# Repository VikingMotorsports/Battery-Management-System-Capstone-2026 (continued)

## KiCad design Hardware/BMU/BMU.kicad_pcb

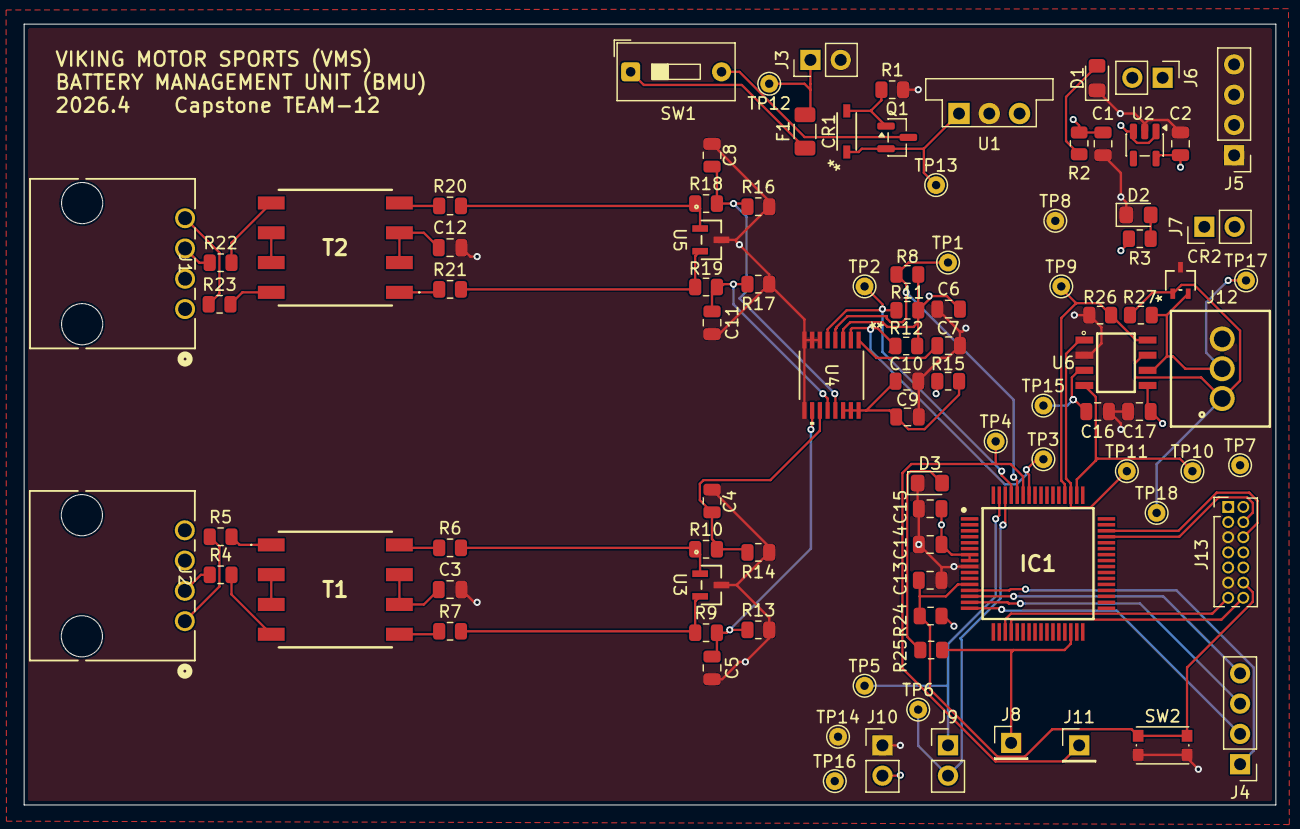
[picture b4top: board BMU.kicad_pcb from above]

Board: 4 copper layers, 105.0 x 65.5 mm, 93 parts (0 on the bottom side), 58 nets.

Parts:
C1, C2, C14: 1u; C_0805_2012Metric
C3, C4, C5, C8, C11, C12: 100pF; C_0805_2012Metric
C6, C10: 0.1u; C_0805_2012Metric
C7, C9: 0.22u; C_0805_2012Metric
C13, C15, C16, C17: 100n; C_0805_2012Metric
CR1: MMSZ5245B-7-F; SOD123_DIO
CR2: ESDCAN03-2BWY; SOT323-3L_STM
D1, D2, D3: LED; LED_0805_2012Metric_Pad1.15x1.40mm_HandSolder
F1: Fuse; Fuse_1206_3216Metric
IC1: STM32C092RCT6; QFP50P1200X1200X160-64N
J1: HIGH SIDE; CONN_70551-xxxx_04_MOL
J2: LOW SIDE; CONN_70551-xxxx_04_MOL
J3: POWER; PinHeader_1x02_P2.54mm_Vertical
J4: GPIO; PinHeader_1x04_P2.54mm_Vertical
J5: GND; PinHeader_1x04_P2.54mm_Vertical
J6: 5V; PinHeader_1x02_P2.54mm_Vertical
J7: 3V3; PinHeader_1x02_P2.54mm_Vertical
J8: FAULT; PinHeader_1x01_P2.54mm_Vertical
J9: I2C; PinHeader_1x02_P2.54mm_Vertical
J10: SHUNT; PinHeader_1x02_P2.54mm_Vertical
J11: ALERT; PinHeader_1x01_P2.54mm_Vertical
J12: CAN; 691382000003
J13: Conn_ST_STDC14; PinHeader_2x07_P1.27mm_Vertical
Q1: DMP3099L; SOT-23
R1, R8, R11: 100k; R_0805_2012Metric
R2, R3, R25: 1k; R_0805_2012Metric
R4, R5, R6, R7, R20, R21, R22, R23: 0; R_0805_2012Metric
R9, R10, R18, R19: 51; R_0805_2012Metric
R12, R24, R26: 10k; R_0805_2012Metric
R13, R14, R16, R17: 499; R_0805_2012Metric
R15: 10; R_0805_2012Metric
R27: 120; R_0805_2012Metric
SW1: Power Switch; SW_DIP_SPSTx01_Slide_9.78x4.72mm_W7.62mm_P2.54mm
SW2: RESET Switch; SW_Push_1P1T_NO_CK_KMR2
T1, T2: CEP99-102; CEP99102
TP1, TP2, TP3, TP4, TP5, TP6, TP7, TP8, TP9, TP10, TP11, TP12, TP13, TP14, TP15, TP16, TP17, TP18: TestPoint_Small; TestPoint_THTPad_D1.5mm_Drill0.7mm
U1: OKI-78SR-5_1.5-W36-C; Converter_DCDC_Murata_OKI-78SR_Vertical
U2: TLV75533PDBV; SOT-23-5
U3, U5: PESD5V0L2BT; SOT23_NEX
U4: BQ79600PWRQ1; TSSOP16_PW_TEX
U6: MCP2562FDT-H_SN; SOIC127P600X175-8N

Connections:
+3V3: C2.1, C6.2, C14.1, C15.1, C17.1, IC1.7 (VREF+), IC1.8 (VDD/VDDA), J7.1, J7.2, J10.2, J13.3 (VCC), R3.2, R8.1, R11.1, R12.1, R24.1, TP7.1 (1_1), TP16.1 (1_1), U2.5 (OUT), U4.3 (VIO), U6.5 (VIO)
+5V: C1.1, C16.2, J6.1, J6.2, R2.2, R15.1, TP15.1 (1_1), U1.3 (OUT), U2.1 (IN), U2.3 (EN), U6.3 (VDD)
+12V: F1.2, J3.1, TP12.1 (1_1)
/BMU-CAN/CAN_RX: IC1.50 (PD0), TP10.1 (1_1), U6.4 (RXD)
/BMU-CAN/CAN_STBY: IC1.52 (PD2), R26.1, TP9.1 (1_1), U6.8 (STBY)
/BMU-CAN/CAN_TX: IC1.51 (PD1), TP11.1 (1_1), U6.1 (TXD)
/BMU-COM Bridge/COMHN_OPT: R19.1, R21.2, U5.2
/BMU-COM Bridge/COMHP_OPT: R18.1, R20.2, U5.1
/BMU-COM Bridge/COMLN_OPT: R6.2, R10.1, U3.1
/BMU-COM Bridge/COMLP_OPT: R7.2, R9.1, U3.2
/BMU-COM Bridge/FAULT_N: IC1.58 (PB4), R12.2, TP3.1 (1_1), U4.2 (NFAULT)
/BMU-COM Bridge/MISO/TX: IC1.61 (PB7), R11.2, TP2.1 (1_1), U4.5 (TX/MISO)
/BMU-COM Bridge/MOSI/RX: IC1.60 (PB6), R8.2, TP1.1 (1_1), U4.4 (RX/MOSI)
/BMU-MCU/ALERT_SHUNT: IC1.59 (PB5), J11.1 (Pin_1_1), TP4.1 (1_1)
/BMU-MCU/FAULT_LED: IC1.30 (PB10), J8.1 (Pin_1_1), R25.1
/BMU-MCU/GPIO_SPARE1: IC1.14 (PC1), J4.4
/BMU-MCU/GPIO_SPARE2: IC1.15 (PC2), J4.3
/BMU-MCU/GPIO_SPARE3: IC1.16 (PC3), J4.2
/BMU-MCU/SHUTDOWN: IC1.13 (PC0), J4.1
/BMU-POWER/VIN_PROTECTED: CR1.1, Q1.2 (S), TP13.1 (1_1), U1.1 (IN)
/High COMHN: J1.4, R23.1
/High COMHP: J1.3, R22.1
/J4_CANH: CR2.1, J12.1, R27.2, TP18.1 (1_1), U6.7 (CANH)
/J4_CANL: CR2.2, J12.2, R27.1, TP17.1 (1_1), U6.6 (CANL)
/LOW COMLN: J2.1, R5.1
/LOW COMLP: J2.2, R4.1
/SCL_STM32: IC1.62 (PB8), J9.2, TP6.1 (1_1)
/SDA_STM32: IC1.63 (PB9), J9.1, TP5.1 (1_1)
COMHN: C11.1, R17.2, R19.2, U4.12 (COMHN)
COMHP: C8.1, R16.1, R18.2, U4.13 (COMHP)
COMLN: C4.1, R10.2, R14.2, U4.11 (COMLN)
COMLP: C5.1, R9.2, R13.1, U4.10 (COMLP)
GND: C1.2, C2.2, C3.2, C4.2, C5.2, C6.1, C7.2, C8.2, C9.2, C10.2, C11.2, C12.2, C13.1, C14.2, C15.2, C16.1, C17.2, CR2.3, D1.1 (K), D2.1 (K), D3.1 (K), IC1.9 (VSS/VSSA), J3.2, J5.1, J5.2, J5.3, J5.4, J10.1, J12.3, J13.5 (GND), J13.11 (GNDDetect), R1.2, R13.2, R14.1, R16.2, R17.1, R26.2, SW2.2 (B), TP8.1 (1_1), TP14.1 (1_1), U1.2 (GND), U2.2 (GND), U3.3, U4.6 (SCLK), U4.7 (NCS), U4.8 (NUART/SPI_(SPI_RDY)), U4.9 (GND), U5.3, U6.2 (VSS)
unnamed: C3.1, T1.6, T1.7
unnamed: C12.1, T2.2, T2.3
unnamed: D1.2 (A), R2.1
unnamed: D2.2 (A), R3.1
unnamed: D3.2 (A), R25.2
unnamed: IC1.19 (PA2), J13.13 (VCP_RX)
unnamed: IC1.20 (PA3), J13.14 (VCP_TX)
unnamed: IC1.45 (PA13), J13.4 (JTMS/SWDIO)
unnamed: IC1.46 (PA14-BOOT0), J13.6 (JCLK/SWCLK)
unnamed: C13.2, IC1.12 (PF2-NRST), J13.12 (~RST), R24.2, SW2.1 (A)
unnamed: Q1.3 (D), SW1.2 (B)
unnamed: CR1.2, Q1.1 (G), R1.1
unnamed: R4.2, T1.4
unnamed: R5.2, T1.1
unnamed: R6.1, T1.8
unnamed: R7.1, T1.5
unnamed: R20.1, T2.4
unnamed: R21.1, T2.1
unnamed: R22.2, T2.5
unnamed: R23.2, T2.8
unnamed: F1.1, SW1.1 (A)
unnamed: T1.2, T1.3
unnamed: T2.6, T2.7
unnamed: C9.1, C10.1, R15.2, U4.14 (CVDD), U4.15 (BAT), U4.16 (INH)
unnamed: C7.1, U4.1 (DVDD)

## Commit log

2026-05-01 Test Plan First Draft
2026-05-02 update power part
2026-05-03 finish BMU, add test point + comment
2026-05-03 Update shunt circuit KiCad files
2026-05-04 Update monitor hardware files
2026-05-07 Both boards are now fully completed: the BMU and CMU.
2026-05-07 add mounting holes
2026-05-08 update layout
2026-05-09 Schematic polish -- fixed to best standards, cleaned up for ERCs, etc
2026-05-09 add libraries for BMU+CMU
2026-05-09 Update shunt circuit hardware files
2026-05-09 Add shunt circuit custom libraries
2026-05-09 A bit of layout polish and bring in the correct stackup and DRUs from OSH Park
2026-05-09 Replace shunt circuit libraries and update KiCad files
2026-05-10 update libraries+bmu
2026-05-10 update CMU
2026-05-11 Added fault configuration and handling as well as reading and clearing
2026-05-11 Refactored and cleaned up faults module
2026-05-11 edit footprint library
2026-05-12 Added a debug module to more cleanly print debug outputs to serial monitor
2026-05-12 add via for bmu
2026-05-12 Added and configured OV and UV fault detection
2026-05-13 Added and configured OT and UT fault detection
2026-05-14 Fixed shunt board, fixed .gitignore.
2026-05-14 Rounded board outline
2026-05-14 Schematic cleanup; lots of missing library files
2026-05-14 fix library paths
2026-05-15 Fixed all missing symbol and footprint libraries
2026-05-17 Added and configured cell balancing
2026-05-17 Added configuration option to toggle cell balancing functionality
2026-05-18 Refactored protocol and register map modules
2026-05-18 Added I2C communication and INA238 protocol support
2026-05-18 Added current monitoring functionality and current debug printing
2026-05-19 doubled up pin for bmu
2026-05-19 add bom
2026-05-19 Add macOS Finder metadata files to .gitignore
2026-05-20 Added ability to toggle battery monitoring functionalities
2026-05-20 Added INA238 fault monitoring functionality
2026-05-20 Refactored fault monitoring dependencies and conditions
2026-05-20 Fixed conditional debug fault printing
2026-05-20 Added and configured OCD fault detection
2026-05-21 CAN Test Draft
2026-05-22 VCUModule template Added
2026-05-23 Pass point for CAN
2026-05-27 File Renaming
2026-05-27 updated cmu BOM
2026-05-27 Added CAN-FD BMS telemetry transmission
2026-05-27 Big schematic cleanup - made into hierarchical schematic, lots of checking on power, more text notes.
2026-05-27 Adjusted OV and UV thresholds
2026-05-27 A bit more schematic polishing
2026-05-27 Add keepout rules for high voltage areas
2026-05-27 fix BOM
2026-05-28 Update shunt circuit files and add BOM
2026-05-28 Remove shunt BOM CSV from repo
2026-05-28 updated cmu layout
2026-05-28 change iso+update cmu BOM
2026-05-28 finish! update bmu layout+BOM
2026-05-30 Extra Documentation Added
2026-05-30 add jumper+ change SW for bmu
2026-06-01 Final Report Rough Draft
2026-06-02 Made a nicer symbol, cleaned up ERC, cleaned up DRC, fabricated
2026-06-02 Rounded corners, better board silk, stitching vias
2026-06-02 Polishing, BOM fixes, stitching
2026-06-05 Added configuration option to toggle CAN telemetry functionality
2026-06-05 Added CAN telemetry debug printing functionality
2026-06-05 Added log message for CAN telemetry initialization status
2026-06-06 Added CAN telemetry frame metadata to debug output
2026-06-06 Increased main thread stack size
2026-06-06 Added classic CAN telemetry compatibility
2026-06-06 Refactored error log messages for CAN mode and payload size
2026-06-06 Added vulCAN classic CAN listener script
2026-06-07 Refactored BQ796xx register map to only include register address and not control values
2026-06-10 Poster Moved to Google Drive
2026-06-12 Final Report moved to Drive and Interactive BOMs added
2026-06-12 Final submission for Capstone
2026-06-14 Final Draft of Report
